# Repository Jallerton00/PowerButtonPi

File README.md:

# PowerButtonPi

Use a Pi Pico to emulate a PC power button (and drive some LEDs).

## Hardware

[PDF Schematic](/hardware/schematic.pdf)

(ATX interaction ~~stolen~~ borrowed from [PiKVM](https://docs.pikvm.org/v1/#setting-up-the-hardware)).

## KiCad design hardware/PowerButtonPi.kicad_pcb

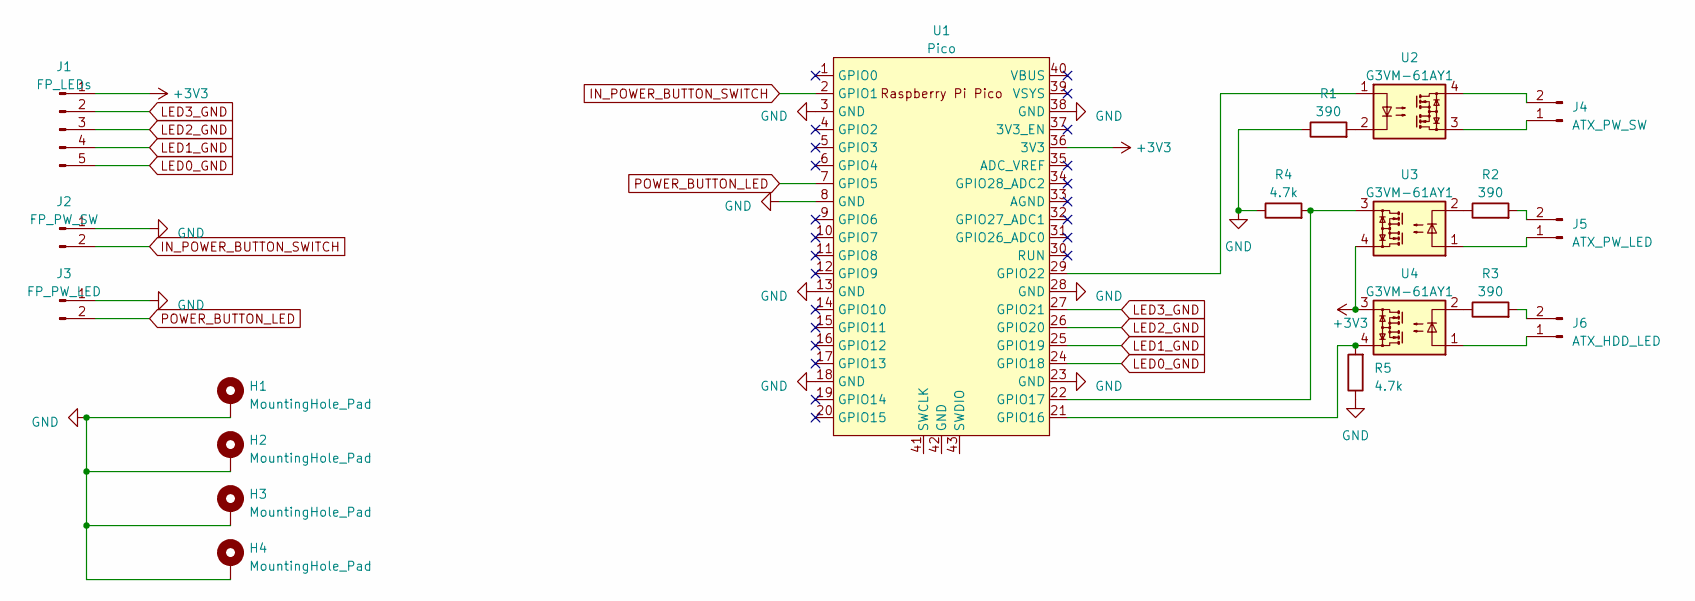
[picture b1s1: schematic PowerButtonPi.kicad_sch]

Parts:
H1, H2, H3, H4: MountingHole_Pad; MountingHole_3.2mm_M3_Pad
J1: FP_LEDs; PinHeader_1x05_P2.54mm_Vertical
J2: FP_PW_SW; PinHeader_1x02_P2.54mm_Vertical
J3: FP_PW_LED; PinHeader_1x02_P2.54mm_Vertical
J4: ATX_PW_SW; PinHeader_1x02_P2.54mm_Vertical
J5: ATX_PW_LED; PinHeader_1x02_P2.54mm_Vertical
J6: ATX_HDD_LED; PinHeader_1x02_P2.54mm_Vertical
R1, R2, R3: 390; R_Axial_DIN0207_L6.3mm_D2.5mm_P7.62mm_Horizontal
R4, R5: 4.7k; R_Axial_DIN0207_L6.3mm_D2.5mm_P7.62mm_Horizontal
U1: Pico; RPi_Pico_SMD_TH
U2, U3, U4: G3VM-61AY1; DIP-4_W7.62mm

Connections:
+3V3: J1.1, U1.36 (3V3), U3.4, U4.3
GND: H1.1, H2.1, H3.1, H4.1, J2.1, J3.1, R1.1, R4.1, R5.1, U1.3 (GND), U1.8 (GND), U1.13 (GND), U1.18 (GND), U1.23 (GND), U1.28 (GND), U1.38 (GND)
IN_POWER_BUTTON_SWITCH: J2.2, U1.2 (GPIO1)
LED0_GND: J1.5, U1.24 (GPIO18)
LED1_GND: J1.4, U1.25 (GPIO19)
LED2_GND: J1.3, U1.26 (GPIO20)
LED3_GND: J1.2, U1.27 (GPIO21)
unnamed: J4.1, U2.3
unnamed: J4.2, U2.4
unnamed: J5.1, U3.1
unnamed: J5.2, R2.2
unnamed: J6.1, U4.1
unnamed: J6.2, R3.2
unnamed: R1.2, U2.2
unnamed: R2.1, U3.2
unnamed: R3.1, U4.2
unnamed: R5.2, U1.21 (GPIO16), U4.4
unnamed: R4.2, U1.22 (GPIO17), U3.3
unnamed: U1.29 (GPIO22), U2.1
POWER_BUTTON_LED: J3.2, U1.7 (GPIO5)

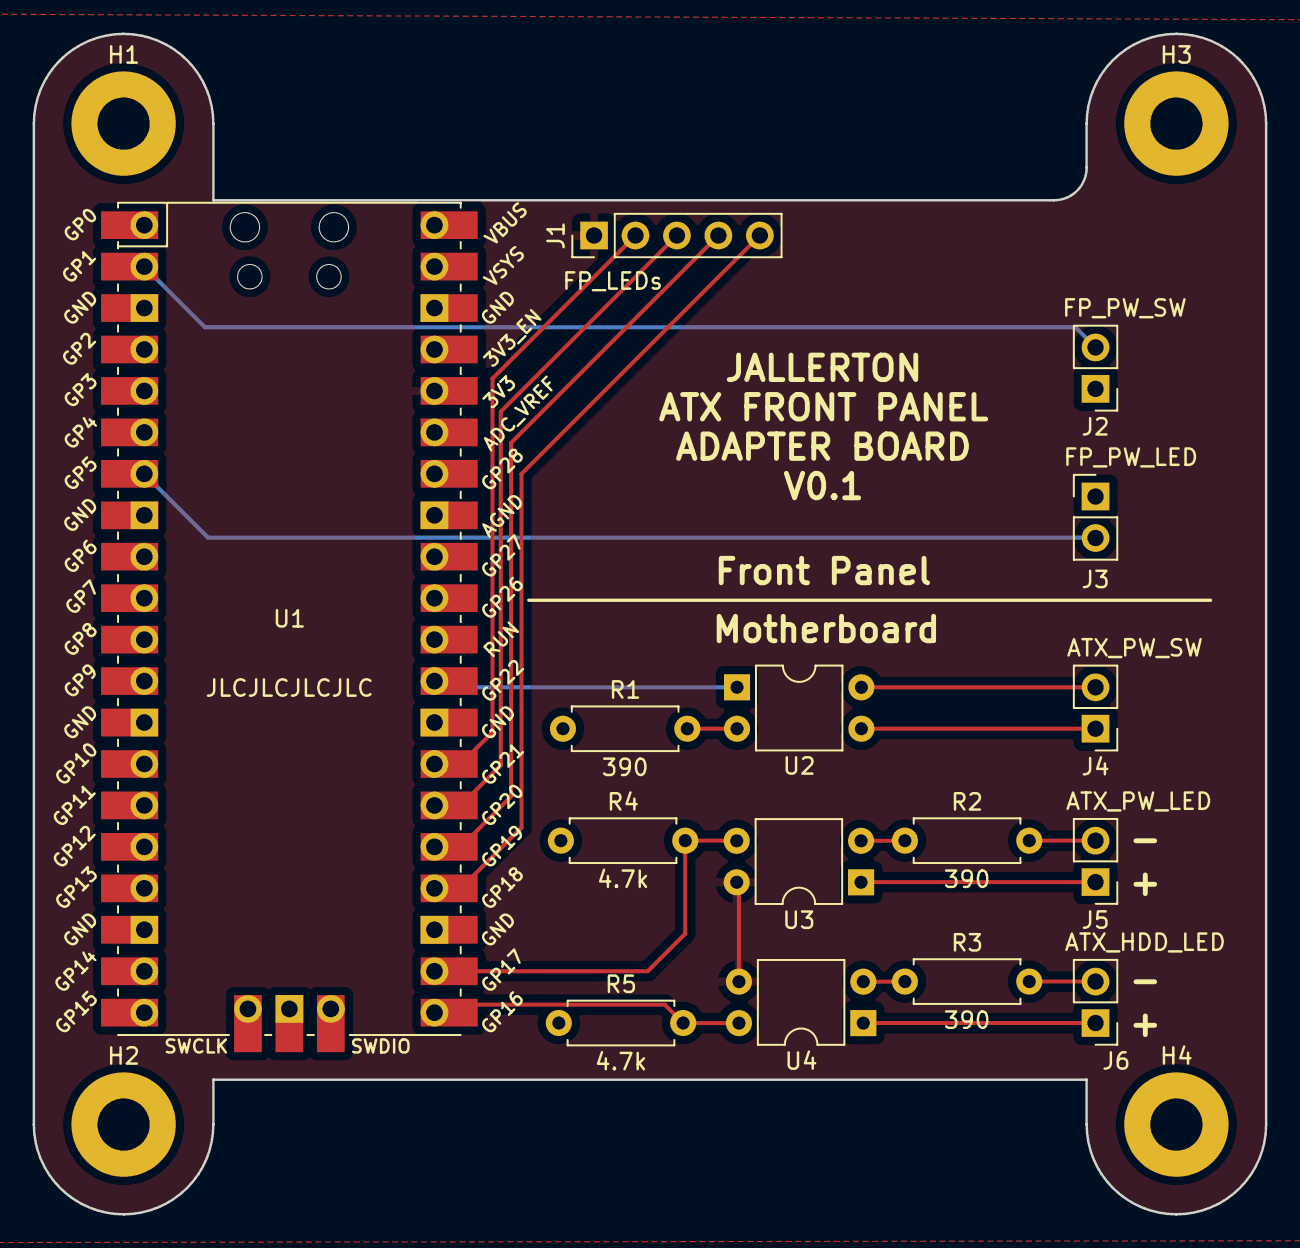
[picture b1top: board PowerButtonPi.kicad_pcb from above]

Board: 2 copper layers, 75.5 x 72.3 mm, 19 parts (0 on the bottom side), 20 nets.

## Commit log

2024-04-21 LEDs go up and down
2024-04-21 Comments
2024-05-01 PCB order
2024-05-01 Test hardware
2024-05-05 fixes & show HDD LED
2024-05-05 Add Github Action for KiCAD images and exports
    Create main.yml
    Create README.md
    Update main.yml
    Update main.yml
    Update main.yml
    remove old manu files
2024-05-05 Update images, schematic and gerbers
2024-05-05 Update automation to only run on HW change
2024-05-05 README - add animation
2024-05-05 Add ability to run automation manually
2024-05-05 Test
2024-05-05 Add Github Action for KiCAD images and exports
    Add Github Action for KiCAD images and exports
    Create main.yml
    Create README.md
    Update main.yml
    Update main.yml
    Update main.yml
2024-05-06 Add setLED method
2024-05-06 Fix setting LED
2024-05-06 Add link to PiKVM
2024-06-17 Mac Mini Auto Power On
    Add auto power on to Mac Mini by soldering in place of the power button.
    Power the Pico from another PC on the same supply to the Mini, then the Mini turns on 1s after the Pico receives power.
